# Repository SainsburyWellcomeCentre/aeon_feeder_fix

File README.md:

# aeon_beambreak_filter

This IR beam break processing code is a workaround to filter the adaptive threshold signal in the case where the beam is blocked by accidental obstruction. The following state machine describes the filtering operation:

```mermaid
stateDiagram-v2
    [*] --> Ready
    Ready --> Pulse: LOW
    Pulse --> Ready: WAIT 3 samples
    Pulse --> Broken: 3 consecutive\n pulses in less\n than 1 second
    Broken --> Ready: 1 second HIGH
    Broken --> Broken: LOW
```

<!-- ## 🌐 View Online (eCAD) -->

## Build your own

Check out the **[latest release](https://github.com/SainsburyWellcomeCentre/aeon_beambreak_filter/releases/latest)** for production Gerbers, BOM, and assembly drawings to build your own beambreak filter.

## 💻 Software Requirements

- **MicroPython** — Firmware runtime on the microcontroller, download the latest UF2 file for the Pi Pico from [MicroPython download page](https://micropython.org/download/rp2-pico/).

To view or edit the source design files:

- **KiCad** _(electronic design)_ — Download via [KiCad](https://www.kicad.org/download/)
- **Inventor 2025+** _(mechanical design)_ — Academic licenses via [Autodesk Education](https://www.autodesk.com/education/free-software/inventor)

## 📜 License

**Sainsbury Wellcome Centre hardware is released under** [Creative Commons Attribution-ShareAlike 4.0 International](http://creativecommons.org/licenses/by-sa/4.0/).

You are free to:

- **Share** — copy and redistribute the material in any medium or format
- **Adapt** — remix, transform, and build upon the material for any purpose

Under the following terms:

- **Attribution** — Give appropriate credit, link to the license, and indicate changes.
- **ShareAlike** — Distribute your contributions under the same license.
- **No additional restrictions** — Don't apply legal or technological measures that prevent others from doing anything the license permits.

> For the full legal text, see [LICENSE](LICENSE).

## 📧 Contact

- **Author**: [Sainsbury Wellcome Centre FabLabs](https://www.sainsburywellcome.org/content/fablab)
- **Email**: [swc.fablabs@ucl.ac.uk](mailto:swc.fablabs@ucl.ac.uk)
- **Website**: [FabLabs Documentation](https://sainsburywellcomecentre.github.io/fablabs-documentation/aeon_beambreak_filter)

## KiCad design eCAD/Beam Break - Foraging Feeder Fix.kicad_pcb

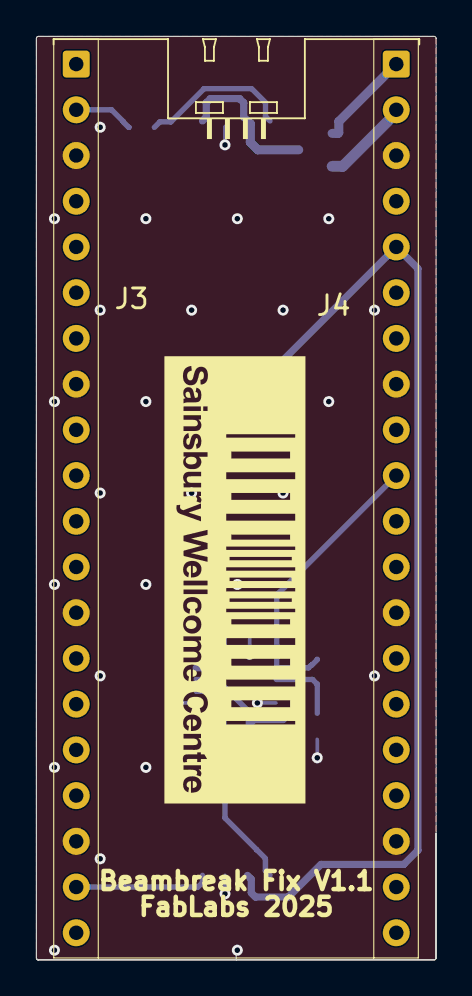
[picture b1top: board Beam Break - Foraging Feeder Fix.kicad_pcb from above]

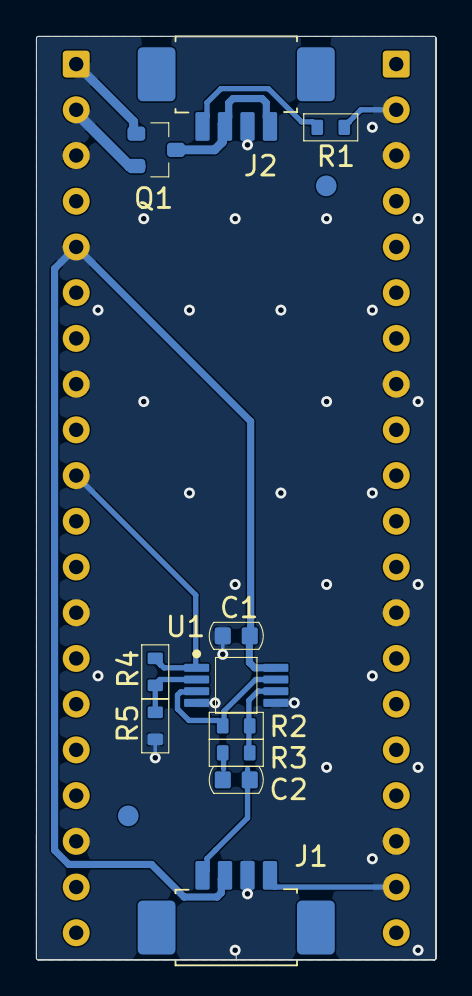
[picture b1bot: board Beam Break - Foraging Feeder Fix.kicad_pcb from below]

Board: 2 copper layers, 22.2 x 51.3 mm, 15 parts (13 on the bottom side), 14 nets.

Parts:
C1: C0603-100nF-50V; CAP_CHIP_0603
C2: C0603-1nF-50V; CAP_CHIP_0603
FID1, FID2: FID-ROUND; Fid_Round
J1, J2: Molex-1.25-R-4P; MOLEX_1.25_R_4P
J3: PICO-L; FM_2.54_1X20P
J4: PICO-R; FM_2.54_1X20P
Q1: AO3401A; SOT23
R1: R0603-150R; RES_CHIP_0603
R2, R3: R0603-1M; RES_CHIP_0603
R4: R0603-100K; RES_CHIP_0603
R5: R0603-4K7; RES_CHIP_0603
U1: AD8606; VSSOP8_3X3_0.65E

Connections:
3V3: C1.2, J1.2, J4.5, U1.8
3V3in: J2.1, J2.3, Q1.3
BEAM BREAK: J3.2, R1.1
GND: C1.1, J1.3, J2.2, J3.3, J3.8, J3.13, J3.18, J4.3, J4.8, J4.13, J4.18, R5.1, U1.4, U1.5
IR_LED: J1.4, J3.19
IR_PT: C2.1, J1.1
IR_PT_FILTERED: J4.10, R4.2, U1.1
NetC2_2: C2.2, R3.1
NetJ2_4: J2.4, R1.2
NetR2_1: R2.1, R3.2, U1.6
NetR2_2: R2.2, U1.3, U1.7
NetR4_1: R4.1, R5.2, U1.2
VBUS: J4.1, Q1.1
VSYS: J4.2, Q1.2

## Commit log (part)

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2023-11-16 Added files and organised repo
2023-12-12 Update README with steps for firmware uploading
2023-12-13 initial micropython-microharp code version
2023-12-20 Hold line HIGH for X consecutive inactive readings
2023-12-27 Add state machine to handle blocked chute
2023-12-28 Ensure out is kept HIGH when entering broken state
2024-03-13 Update LICENSE
2024-03-13 Update LICENSE (#2)
